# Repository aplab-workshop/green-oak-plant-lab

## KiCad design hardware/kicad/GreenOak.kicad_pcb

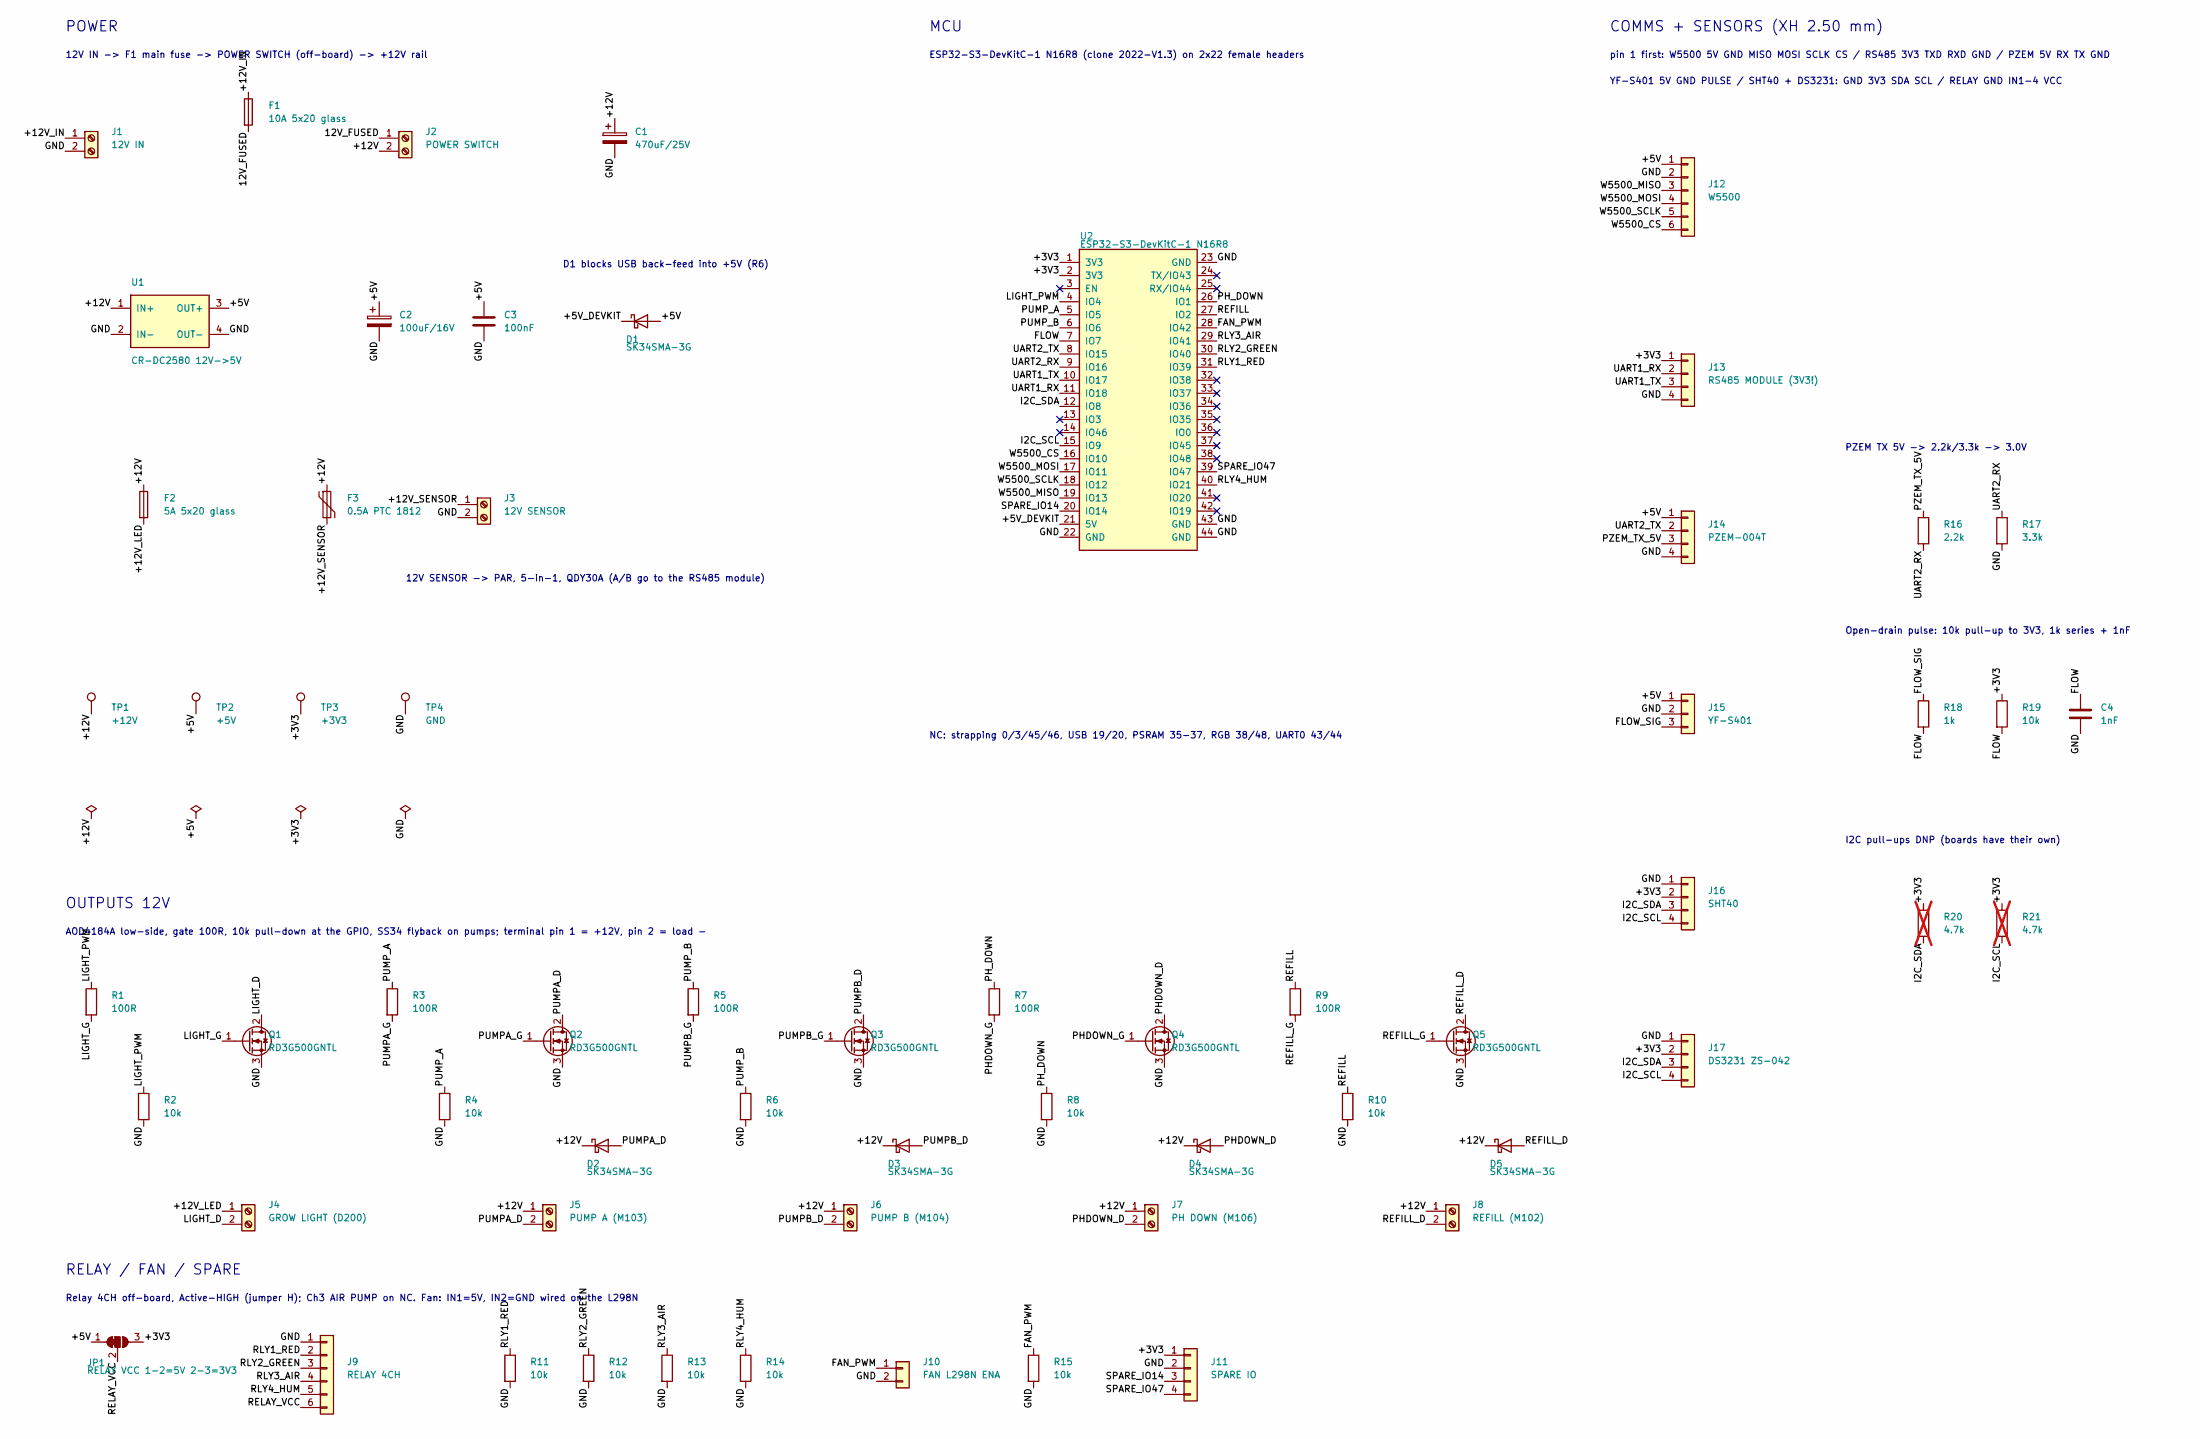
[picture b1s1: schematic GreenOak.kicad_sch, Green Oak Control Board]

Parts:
C1: 470uF/25V; CP_Radial_D10.0mm_P5.00mm; MPN EGK477M1EG16RRSMP
C2: 100uF/16V; CP_Radial_D6.3mm_P2.50mm; MPN RE1CM101E110T
C3: 100nF; C_0805_2012Metric; MPN 08055C104K4T2A
C4: 1nF; C_0805_2012Metric; MPN 0805N102J500CT
D1, D2, D3, D4, D5: SK34SMA-3G; D_SMA; MPN SK34SMA-3G
F1: 10A 5x20 glass; Fuseholder_5x20_BLX-A
F2: 5A 5x20 glass; Fuseholder_5x20_BLX-A
F3: 0.5A PTC 1812; Fuse_1812_4532Metric
J1: 12V IN; TerminalBlock_Phoenix_MKDS-1,5-2-5.08_1x02_P5.08mm_Horizont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
J2: POWER SWITCH; TerminalBlock_Phoenix_MKDS-1,5-2-5.08_1x02_P5.08mm_Horizont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
J3: 12V SENSOR; TerminalBlock_Phoenix_MKDS-1,5-2-5.08_1x02_P5.08mm_Horizont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
J4: GROW LIGHT (D200); TerminalBlock_Phoenix_MKDS-1,5-2-5.08_1x02_P5.08mm_Horizont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
J5: PUMP A (M103); TerminalBlock_Phoenix_MKDS-1,5-2-5.08_1x02_P5.08mm_Horizont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
J6: PUMP B (M104); TerminalBlock_Phoenix_MKDS-1,5-2-5.08_1x02_P5.08mm_Horizont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
J7: PH DOWN (M106); TerminalBlock_Phoenix_MKDS-1,5-2-5.08_1x02_P5.08mm_Horizont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
J8: REFILL (M102); TerminalBlock_Phoenix_MKDS-1,5-2-5.08_1x02_P5.08mm_Horizont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
J9: RELAY 4CH; JST_XH_B6B-XH-A_1x06_P2.50mm_Vertical
J10: FAN L298N ENA; JST_XH_B2B-XH-A_1x02_P2.50mm_Vertical
J11: SPARE IO; JST_XH_B4B-XH-A_1x04_P2.50mm_Vertical
J12: W5500; JST_XH_B6B-XH-A_1x06_P2.50mm_Vertical
J13: RS485 MODULE (3V3!); JST_XH_B4B-XH-A_1x04_P2.50mm_Vertical
J14: PZEM-004T; JST_XH_B4B-XH-A_1x04_P2.50mm_Vertical
J15: YF-S401; JST_XH_B3B-XH-A_1x03_P2.50mm_Vertical
J16: SHT40; JST_XH_B4B-XH-A_1x04_P2.50mm_Vertical
J17: DS3231 ZS-042; JST_XH_B4B-XH-A_1x04_P2.50mm_Vertical
JP1: RELAY VCC 1-2=5V 2-3=3V3; SolderJumper-3_P1.3mm_Bridged12_Pad1.0x1.5mm
Q1, Q2, Q3, Q4, Q5: RD3G500GNTL; TO-252-2; MPN RD3G500GNTL
R1, R3, R5, R7, R9: 100R; R_0805_2012Metric; MPN 0805W8F1000T5E
R2, R4, R6, R8, R10, R11, R12, R13, R14, R15, R19: 10k; R_0805_2012Metric; MPN 0805W8F1002T5E
R16: 2.2k; R_0805_2012Metric; MPN 0805W8F2201T5E
R17: 3.3k; R_0805_2012Metric; MPN 0805W8F3301T5E
R18: 1k; R_0805_2012Metric; MPN 0805W8F1001T5E
R20, R21: 4.7k; R_0805_2012Metric; MPN 0805W8F4701T5E; not fitted
TP1: +12V; TestPoint_THTPad_D2.0mm_Drill1.0mm
TP2: +5V; TestPoint_THTPad_D2.0mm_Drill1.0mm
TP3: +3V3; TestPoint_THTPad_D2.0mm_Drill1.0mm
TP4: GND; TestPoint_THTPad_D2.0mm_Drill1.0mm
U1: CR-DC2580 12V->5V; CR-DC2580_Module
U2: ESP32-S3-DevKitC-1 N16R8; ESP32-S3-DevKitC-1_Socket

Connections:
12V_FUSED: F1.2, J2.1
+3V3: J11.1, J13.1, J16.2, J17.2, JP1.3 (B), R19.1, R20.1, R21.1, TP3.1, U2.1 (3V3), U2.2 (3V3)
+5V: C2.1, C3.1, D1.2 (A), J12.1, J14.1, J15.1, JP1.1 (A), TP2.1, U1.3 (OUT+)
+5V_DEVKIT: D1.1 (K), U2.21 (5V)
+12V: C1.1, D2.1 (K), D3.1 (K), D4.1 (K), D5.1 (K), F2.1, F3.1, J2.2, J5.1, J6.1, J7.1, J8.1, TP1.1, U1.1 (IN+)
+12V_IN: F1.1, J1.1
+12V_LED: F2.2, J4.1
+12V_SENSOR: F3.2, J3.1
FAN_PWM: J10.1, R15.1, U2.28 (IO42)
FLOW: C4.1, R18.2, R19.2, U2.7 (IO7)
FLOW_SIG: J15.3, R18.1
GND: C1.2, C2.2, C3.2, C4.2, J1.2, J3.2, J9.1, J10.2, J11.2, J12.2, J13.4, J14.4, J15.2, J16.1, J17.1, Q1.3 (S), Q2.3 (S), Q3.3 (S), Q4.3 (S), Q5.3 (S), R2.2, R4.2, R6.2, R8.2, R10.2, R11.2, R12.2, R13.2, R14.2, R15.2, R17.2, TP4.1, U1.2 (IN-), U1.4 (OUT-), U2.22 (GND), U2.23 (GND), U2.43 (GND), U2.44 (GND)
I2C_SCL: J16.4, J17.4, R21.2, U2.15 (IO9)
I2C_SDA: J16.3, J17.3, R20.2, U2.12 (IO8)
LIGHT_D: J4.2, Q1.2 (D)
LIGHT_G: Q1.1 (G), R1.2
LIGHT_PWM: R1.1, R2.1, U2.4 (IO4)
PHDOWN_D: D4.2 (A), J7.2, Q4.2 (D)
PHDOWN_G: Q4.1 (G), R7.2
PH_DOWN: R7.1, R8.1, U2.26 (IO1)
PUMPA_D: D2.2 (A), J5.2, Q2.2 (D)
PUMPA_G: Q2.1 (G), R3.2
PUMPB_D: D3.2 (A), J6.2, Q3.2 (D)
PUMPB_G: Q3.1 (G), R5.2
PUMP_A: R3.1, R4.1, U2.5 (IO5)
PUMP_B: R5.1, R6.1, U2.6 (IO6)
PZEM_TX_5V: J14.3, R16.1
REFILL: R9.1, R10.1, U2.27 (IO2)
REFILL_D: D5.2 (A), J8.2, Q5.2 (D)
REFILL_G: Q5.1 (G), R9.2
RELAY_VCC: J9.6, JP1.2 (C)
RLY1_RED: J9.2, R11.1, U2.31 (IO39)
RLY2_GREEN: J9.3, R12.1, U2.30 (IO40)
RLY3_AIR: J9.4, R13.1, U2.29 (IO41)
RLY4_HUM: J9.5, R14.1, U2.40 (IO21)
SPARE_IO14: J11.3, U2.20 (IO14)
SPARE_IO47: J11.4, U2.39 (IO47)
UART1_RX: J13.2, U2.11 (IO18)
UART1_TX: J13.3, U2.10 (IO17)
UART2_RX: R16.2, R17.1, U2.9 (IO16)
UART2_TX: J14.2, U2.8 (IO15)
W5500_CS: J12.6, U2.16 (IO10)
W5500_MISO: J12.3, U2.19 (IO13)
W5500_MOSI: J12.4, U2.17 (IO11)
W5500_SCLK: J12.5, U2.18 (IO12)

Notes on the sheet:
POWER
12V IN -> F1 main fuse -> POWER SWITCH (off-board) -> +12V rail
D1 blocks USB back-feed into +5V (R6)
12V SENSOR -> PAR, 5-in-1, QDY30A (A/B go to the RS485 module)
MCU
ESP32-S3-DevKitC-1 N16R8 (clone 2022-V1.3) on 2x22 female headers
NC: strapping 0/3/45/46, USB 19/20, PSRAM 35-37, RGB 38/48, UART0 43/44
OUTPUTS 12V
AOD4184A low-side, gate 100R, 10k pull-down at the GPIO, SS34 flyback on pumps; terminal pin 1 = +12V, pin 2 = load -
RELAY / FAN / SPARE
Relay 4CH off-board, Active-HIGH (jumper H); Ch3 AIR PUMP on NC. Fan: IN1=5V, IN2=GND wired on the L298N
COMMS + SENSORS (XH 2.50 mm)
pin 1 first: W5500 5V GND MISO MOSI SCLK CS / RS485 3V3 TXD RXD GND / PZEM 5V RX TX GND
YF-S401 5V GND PULSE / SHT40 + DS3231: GND 3V3 SDA SCL / RELAY GND IN1-4 VCC
PZEM TX 5V -> 2.2k/3.3k -> 3.0V
Open-drain pulse: 10k pull-up to 3V3, 1k series + 1nF
I2C pull-ups DNP (boards have their own)

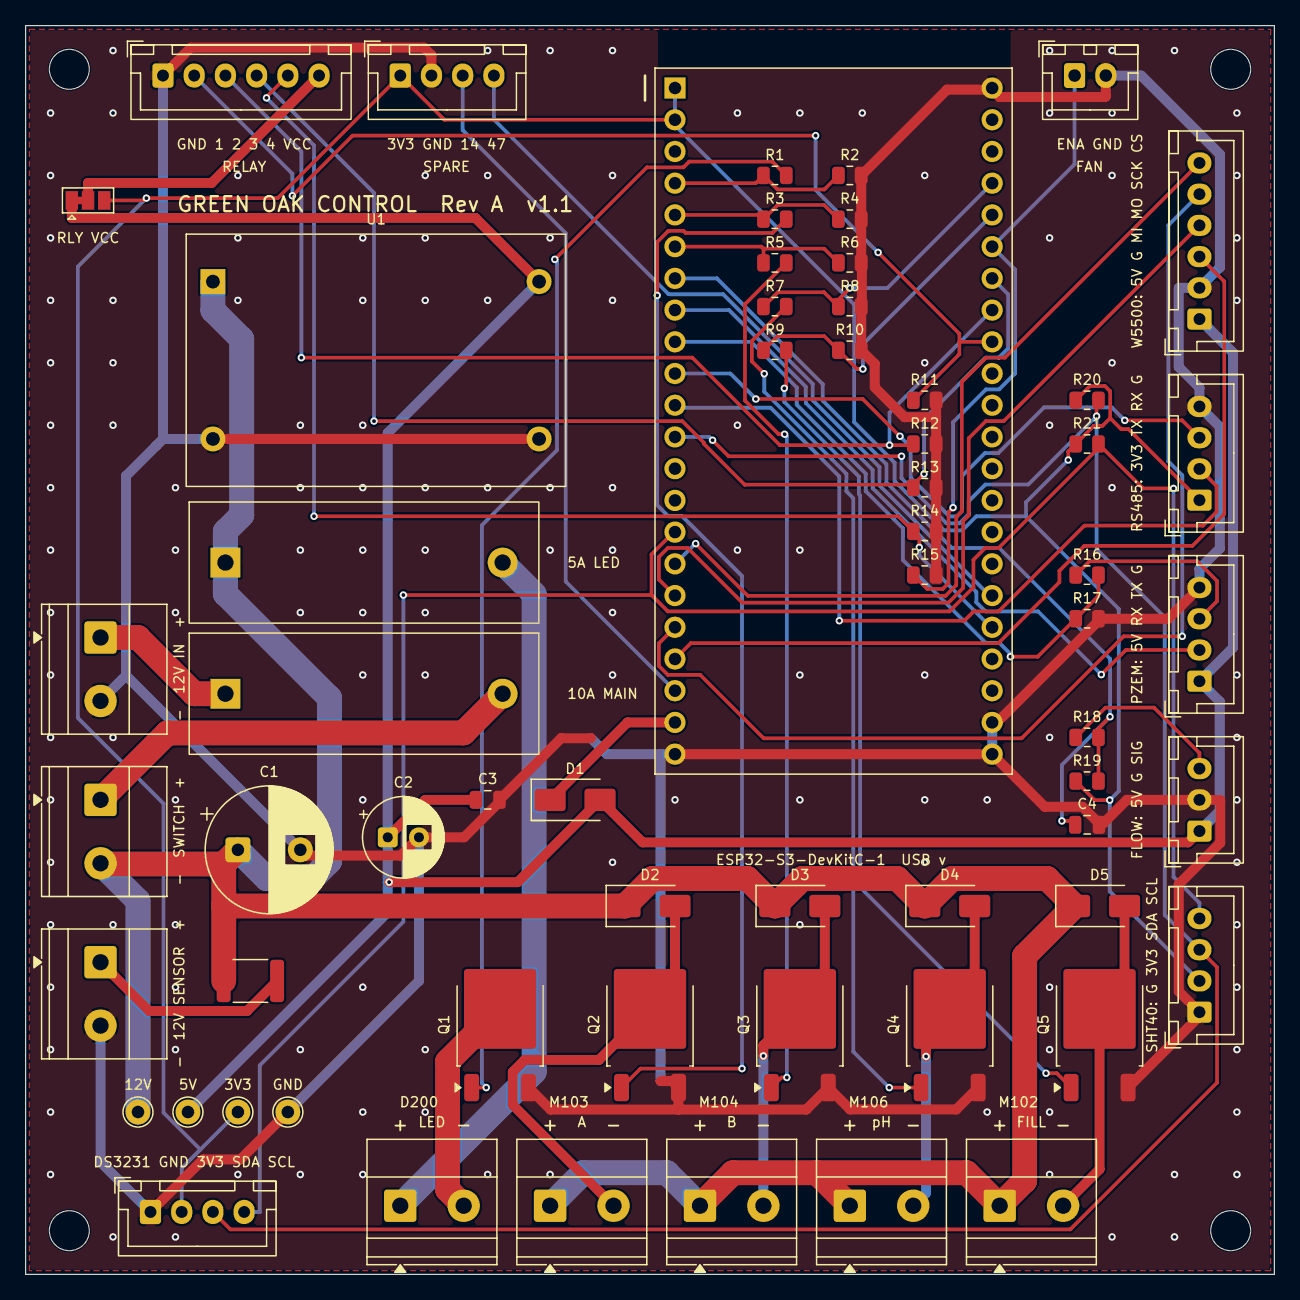
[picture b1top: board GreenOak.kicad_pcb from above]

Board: 2 copper layers, 100.0 x 100.0 mm, 66 parts (0 on the bottom side), 45 nets.

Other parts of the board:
H1, H2, H3, H4: MountingHole_3.2mm_M3

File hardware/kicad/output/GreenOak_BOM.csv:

"Reference","Value","Footprint","MPN","Manufacturer","Supplier","Supplier_PN","QUANTITY","DNP"
"C1","470uF/25V","Capacitor_THT:CP_Radial_D10.0mm_P5.00mm","EGK477M1EG16RRSMP","Samxon","Electronics Source (es.co.th)","0566-0313-9","1",""
"C2","100uF/16V","Capacitor_THT:CP_Radial_D6.3mm_P2.50mm","RE1CM101E110T","AiSHi","Electronics Source (es.co.th)","0825-0097-0","1",""
"C3","100nF","Capacitor_SMD:C_0805_2012Metric","08055C104K4T2A","KYOCERA AVX","Electronics Source (es.co.th)","1721-0040-7","1",""
"C4","1nF","Capacitor_SMD:C_0805_2012Metric","0805N102J500CT","Walsin","Electronics Source (es.co.th)","0328-0182-8","1",""
"D1-D5","SK34SMA-3G","Diode_SMD:D_SMA","SK34SMA-3G","Diotec","Electronics Source (es.co.th)","1998-0113-5","5",""
"F1","10A 5x20 glass","APLab:Fuseholder_5x20_BLX-A","","","","","1",""
"F2","5A 5x20 glass","APLab:Fuseholder_5x20_BLX-A","","","","","1",""
"F3","0.5A PTC 1812","Fuse:Fuse_1812_4532Metric","","","","","1",""
"J1","12V IN","TerminalBlock_Phoenix:TerminalBlock_Phoenix_MKDS-1,5-2-5.08_1x02_P5.08mm_Horizontal","","","","","1",""
"J2","POWER SWITCH","TerminalBlock_Phoenix:TerminalBlock_Phoenix_MKDS-1,5-2-5.08_1x02_P5.08mm_Horizontal","","","","","1",""
"J3","12V SENSOR","TerminalBlock_Phoenix:TerminalBlock_Phoenix_MKDS-1,5-2-5.08_1x02_P5.08mm_Horizontal","","","","","1",""
"J4","GROW LIGHT (D200)","TerminalBlock_Phoenix:TerminalBlock_Phoenix_MKDS-1,5-2-5.08_1x02_P5.08mm_Horizontal","","","","","1",""
"J5","PUMP A (M103)","TerminalBlock_Phoenix:TerminalBlock_Phoenix_MKDS-1,5-2-5.08_1x02_P5.08mm_Horizontal","","","","","1",""
"J6","PUMP B (M104)","TerminalBlock_Phoenix:TerminalBlock_Phoenix_MKDS-1,5-2-5.08_1x02_P5.08mm_Horizontal","","","","","1",""
"J7","PH DOWN (M106)","TerminalBlock_Phoenix:TerminalBlock_Phoenix_MKDS-1,5-2-5.08_1x02_P5.08mm_Horizontal","","","","","1",""
"J8","REFILL (M102)","TerminalBlock_Phoenix:TerminalBlock_Phoenix_MKDS-1,5-2-5.08_1x02_P5.08mm_Horizontal","","","","","1",""
"J9","RELAY 4CH","Connector_JST:JST_XH_B6B-XH-A_1x06_P2.50mm_Vertical","","","","","1",""
"J10","FAN L298N ENA","Connector_JST:JST_XH_B2B-XH-A_1x02_P2.50mm_Vertical","","","","","1",""
"J11","SPARE IO","Connector_JST:JST_XH_B4B-XH-A_1x04_P2.50mm_Vertical","","","","","1",""
"J12","W5500","Connector_JST:JST_XH_B6B-XH-A_1x06_P2.50mm_Vertical","","","","","1",""
"J13","RS485 MODULE (3V3!)","Connector_JST:JST_XH_B4B-XH-A_1x04_P2.50mm_Vertical","","","","","1",""
"J14","PZEM-004T","Connector_JST:JST_XH_B4B-XH-A_1x04_P2.50mm_Vertical","","","","","1",""
"J15","YF-S401","Connector_JST:JST_XH_B3B-XH-A_1x03_P2.50mm_Vertical","","","","","1",""
"J16","SHT40","Connector_JST:JST_XH_B4B-XH-A_1x04_P2.50mm_Vertical","","","","","1",""
"J17","DS3231 ZS-042","Connector_JST:JST_XH_B4B-XH-A_1x04_P2.50mm_Vertical","","","","","1",""
"JP1","RELAY VCC 1-2=5V 2-3=3V3","Jumper:SolderJumper-3_P1.3mm_Bridged12_Pad1.0x1.5mm","","","","","1",""
"Q1-Q5","RD3G500GNTL","Package_TO_SOT_SMD:TO-252-2","RD3G500GNTL","ROHM","Electronics Source (es.co.th)","0176-0653-6","5",""
"R1,R3,R5,R7,R9","100R","Resistor_SMD:R_0805_2012Metric","0805W8F1000T5E","Royalohm","Electronics Source (es.co.th)","0150-1757-1","5",""
"R2,R4,R6,R8,R10-R15,R19","10k","Resistor_SMD:R_0805_2012Metric","0805W8F1002T5E","Royalohm","Electronics Source (es.co.th)","0150-1831-0","11",""
"R16","2.2k","Resistor_SMD:R_0805_2012Metric","0805W8F2201T5E","Royalohm","Electronics Source (es.co.th)","0150-1875-8","1",""
"R17","3.3k","Resistor_SMD:R_0805_2012Metric","0805W8F3301T5E","Royalohm","Electronics Source (es.co.th)","0150-1836-5","1",""
"R18","1k","Resistor_SMD:R_0805_2012Metric","0805W8F1001T5E","Royalohm","Electronics Source (es.co.th)","0150-1758-4","1",""
"R20,R21","4.7k","Resistor_SMD:R_0805_2012Metric","0805W8F4701T5E","Royalohm","Electronics Source (es.co.th)","0150-1882-3","2","DNP"
"TP1","+12V","TestPoint:TestPoint_THTPad_D2.0mm_Drill1.0mm","","","","","1",""
"TP2","+5V","TestPoint:TestPoint_THTPad_D2.0mm_Drill1.0mm","","","","","1",""
"TP3","+3V3","TestPoint:TestPoint_THTPad_D2.0mm_Drill1.0mm","","","","","1",""
"TP4","GND","TestPoint:TestPoint_THTPad_D2.0mm_Drill1.0mm","","","","","1",""
"U1","CR-DC2580 12V->5V","APLab:CR-DC2580_Module","","","","","1",""
"U2","ESP32-S3-DevKitC-1 N16R8","GreenOak:ESP32-S3-DevKitC-1_Socket","","","","","1",""
